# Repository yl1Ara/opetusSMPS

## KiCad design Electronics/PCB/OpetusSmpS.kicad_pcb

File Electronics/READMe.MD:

# [Interactive BOM](https://yl1ara.github.io/opetusSMPS/)

# Shopping lists and sites
components per pcb: https://www.digikey.fi/en/mylists/list/RQZPBNJORH

cables and extras: https://www.digikey.fi/en/mylists/list/IEEER25KGX

ACDC 24V 150W: https://www.mouser.fi/ProductDetail/XP-Power/AHM150PS24?qs=w%2Fv1CP2dgqrkrRjfQac7fA%3D%3D

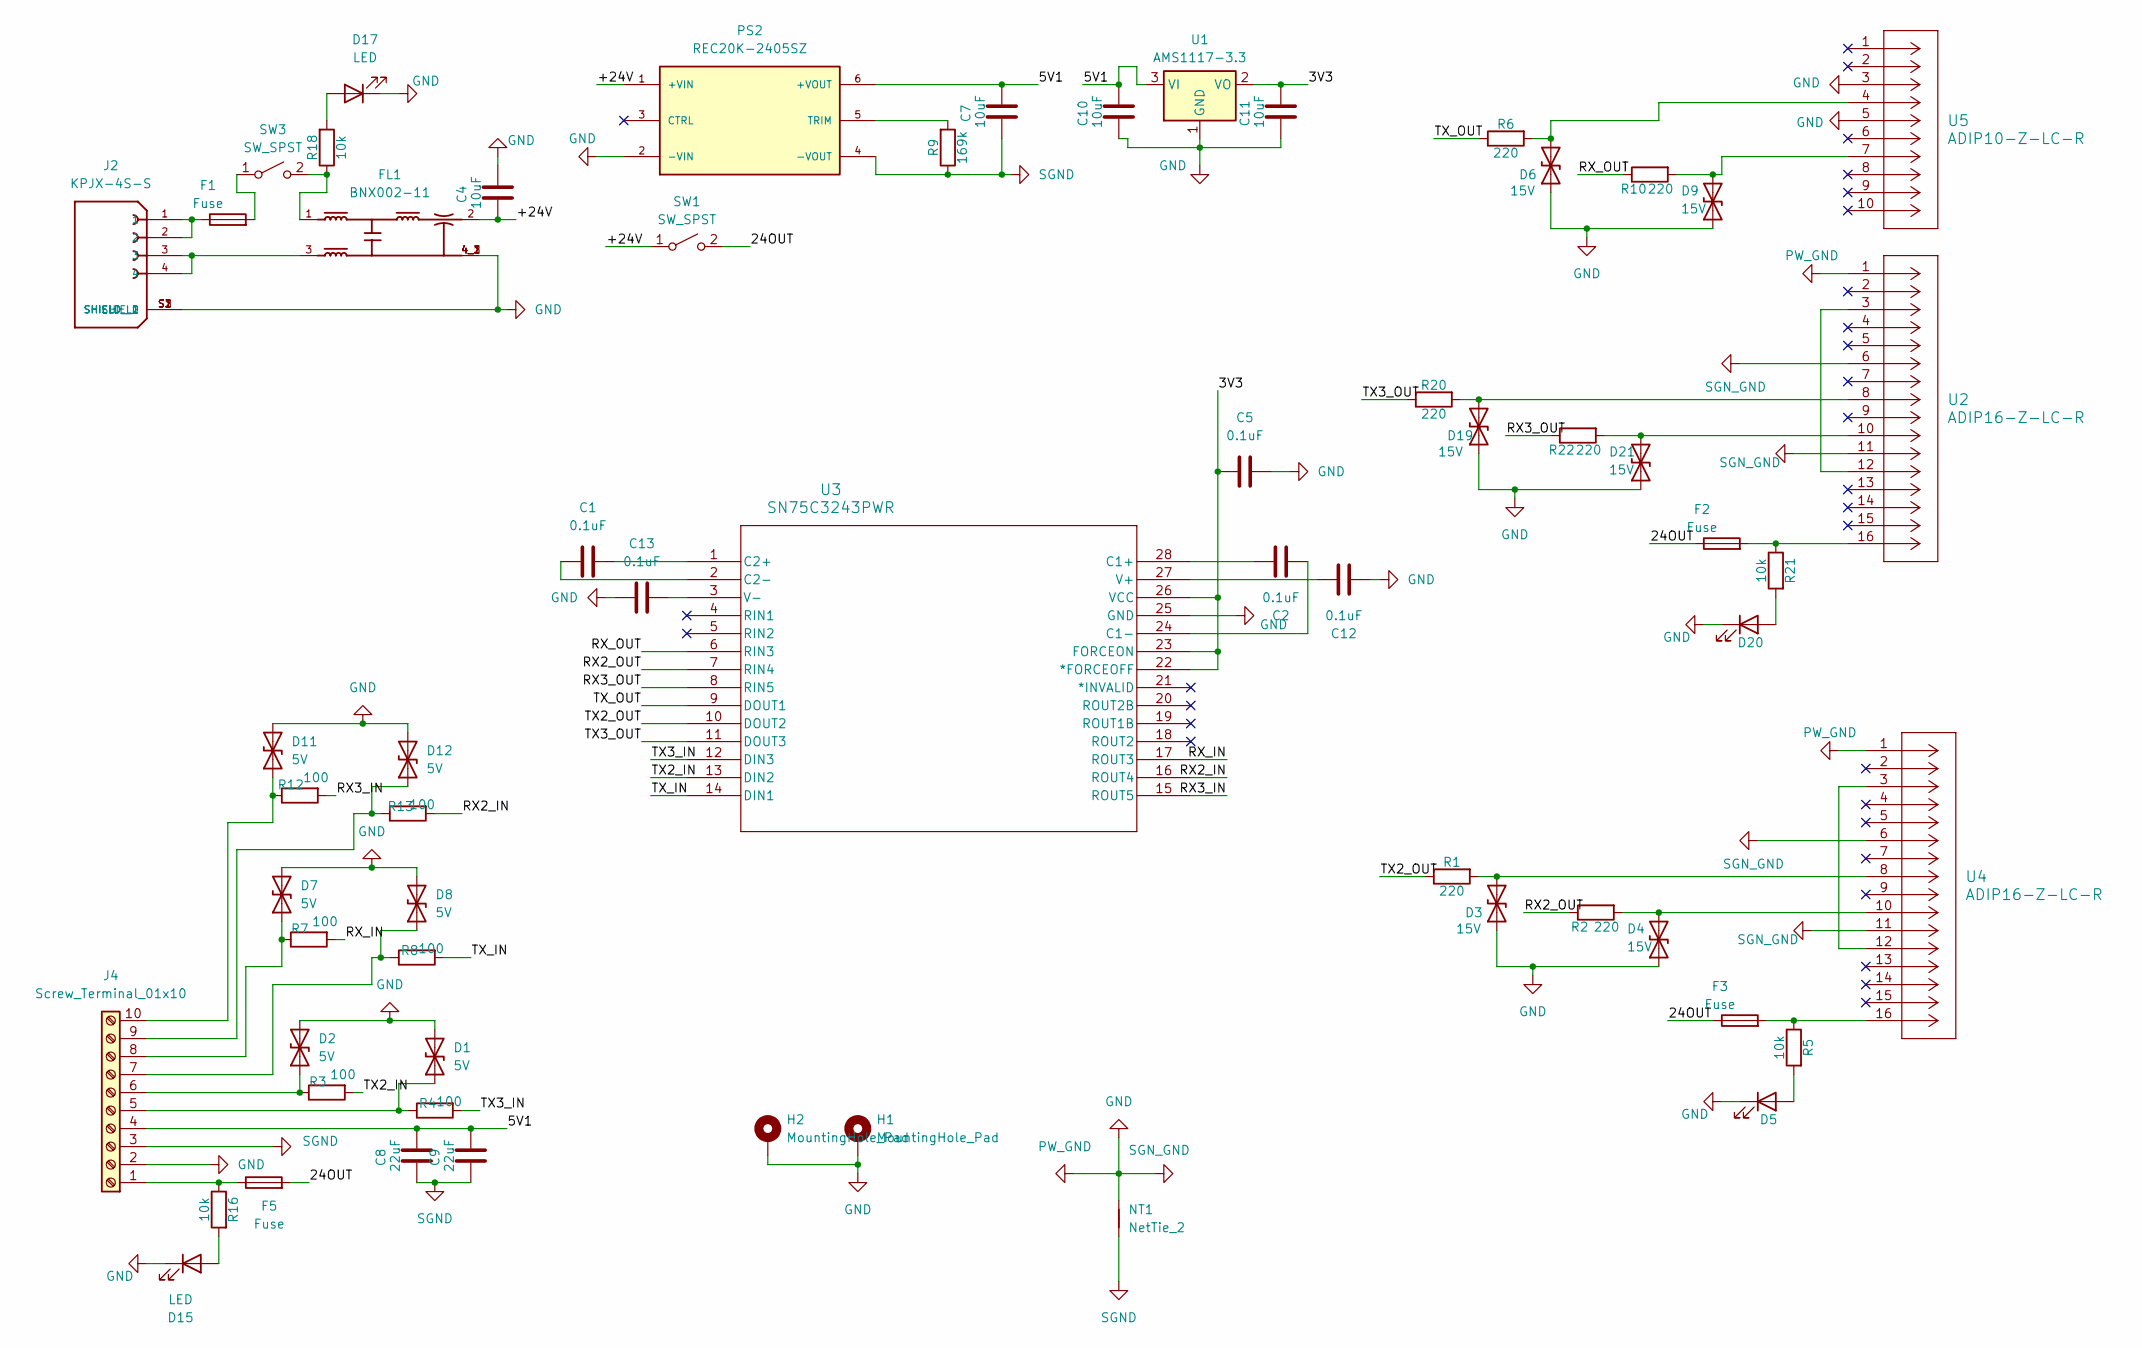
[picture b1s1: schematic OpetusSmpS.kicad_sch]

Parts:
C1, C2, C5, C12, C13: 0.1uF; C_0603_1608Metric_Pad1.08x0.95mm_HandSolder
C4, C7, C10, C11: 10uF; C_0603_1608Metric_Pad1.08x0.95mm_HandSolder
C8, C9: 22uF; C_0603_1608Metric_Pad1.08x0.95mm_HandSolder
D1, D2, D7, D8, D11, D12: 5V; D_SMA
D3, D4, D6, D9, D19, D21: 15V; D_SMB_Handsoldering
D5, D15, D17, D20: LED; PinHeader_1x02_P2.54mm_Vertical
F1: Fuse; Fuseholder_Cylinder-5x20mm_Schurter_0031_8201_Horizontal_Op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
F2, F3, F5: Fuse; FUS_RHEF100_TYCO_TYC
FL1: BNX002-11; FIL_BNX002-11; PARTREV N/A
H1, H2: MountingHole_Pad; MountingHole_4mm_Pad_Via
J2: KPJX-4S-S; KYCON_KPJX-4S-S; PARTREV A15
J4: Screw_Terminal_01x10; TerminalBlock_Phoenix_MKDS-1,5-10_1x10_P5.00mm_Horizontal
NT1: NetTie_2; NetTie-2_THT_Pad0.3mm
PS2: REC20K-2405SZ; CONV_REC20K-2405SZ; PARTREV PRELIMINARY
R1, R2, R6, R10, R20, R22: 220; R_1206_3216Metric_Pad1.30x1.75mm_HandSolder
R3, R4, R7, R8, R12, R13: 100; R_1206_3216Metric_Pad1.30x1.75mm_HandSolder
R5, R16, R18, R21: 10k; R_0805_2012Metric_Pad1.20x1.40mm_HandSolder
R9: 169k; R_0805_2012Metric_Pad1.20x1.40mm_HandSolder
SW1, SW3: SW_SPST; SolderWire-0.1sqmm_1x02_P3.6mm_D0.4mm_OD1mm
U1: AMS1117-3.3; SOT-223-3_TabPin2
U2, U4: ADIP16-Z-LC-R; CON16_300_DIP_AM_ASM
U3: SN75C3243PWR; PW28
U5: ADIP10-Z-LC-R; CON10_300_DIP_AM_ASM

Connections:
/3V3: C5.1, C11.2, U1.2 (VO), U3.22 (*FORCEOFF), U3.23 (FORCEON), U3.26 (VCC)
/5V1: C7.2, C8.2, C9.2, C10.2, J4.4, PS2.6 (+VOUT), U1.3 (VI)
/24OUT: F2.1, F3.1, F5.2, SW1.2 (B)
/+24V: C4.1, FL1.2, PS2.1 (+VIN), SW1.1 (A)
/RX2_IN: R13.2, U3.16 (ROUT4)
/RX2_OUT: R2.1, U3.7 (RIN4)
/RX3_IN: R12.2, U3.15 (ROUT5)
/RX3_OUT: R22.1, U3.8 (RIN5)
/RX_IN: R7.2, U3.17 (ROUT3)
/RX_OUT: R10.1, U3.6 (RIN3)
/TX2_IN: R3.2, U3.13 (DIN2)
/TX2_OUT: R1.1, U3.10 (DOUT2)
/TX3_IN: R4.2, U3.12 (DIN3)
/TX3_OUT: R20.1, U3.11 (DOUT3)
/TX_IN: R8.2, U3.14 (DIN1)
/TX_OUT: R6.1, U3.9 (DOUT1)
GND: C4.2, C5.2, C10.1, C11.1, C12.2, C13.2, D1.2 (A2), D2.2 (A2), D3.1 (A1), D4.1 (A1), D5.1 (K), D6.1 (A1), D7.2 (A2), D8.2 (A2), D9.1 (A1), D11.2 (A2), D12.2 (A2), D15.1 (K), D17.1 (K), D19.1 (A1), D20.1 (K), D21.1 (A1), FL1.4_1, FL1.4_2, FL1.4_3, H1.1, H2.1, J2.S1 (SHIELD), J2.S2 (SHIELD__1), J2.S3 (SHIELD__2), J4.2, NT1.2, PS2.2 (-VIN), U1.1 (GND), U2.1, U2.6, U2.11, U3.25 (GND), U4.1, U4.6, U4.11, U5.3, U5.5
unnamed: D1.1 (A1), J4.5, R4.1
unnamed: D2.1 (A1), J4.6, R3.1
unnamed: D3.2 (A2), R1.2, U4.8
unnamed: D4.2 (A2), R2.2, U4.10
unnamed: D5.2 (A), R5.2
unnamed: D6.2 (A2), R6.2, U5.4
unnamed: D7.1 (A1), J4.8, R7.1
unnamed: D8.1 (A1), J4.7, R8.1
unnamed: D9.2 (A2), R10.2, U5.7
unnamed: D11.1 (A1), J4.10, R12.1
unnamed: D12.1 (A1), J4.9, R13.1
unnamed: D15.2 (A), R16.2
unnamed: D17.2 (A), R18.2
unnamed: D19.2 (A2), R20.2, U2.8
unnamed: D20.2 (A), R21.2
unnamed: D21.2 (A2), R22.2, U2.10
unnamed: F1.1, J2.1, J2.2
unnamed: F2.2, R21.1, U2.16
unnamed: F3.2, R5.1, U4.16
unnamed: FL1.3, J2.3, J2.4
unnamed: F5.1, J4.1, R16.1
unnamed: PS2.5 (TRIM), R9.2
unnamed: F1.2, SW3.1 (A)
unnamed: FL1.1, R18.1, SW3.2 (B)
unnamed: U2.3, U2.12
unnamed: C2.1, U3.28 (C1+)
unnamed: C2.2, U3.24 (C1-)
unnamed: C1.2, U3.1 (C2+)
unnamed: C1.1, U3.2 (C2-)
unnamed: C12.1, U3.27 (V+)
unnamed: C13.1, U3.3 (V-)
unnamed: U4.3, U4.12
SGND: C7.1, C8.1, C9.1, J4.3, NT1.1, PS2.4 (-VOUT), R9.1

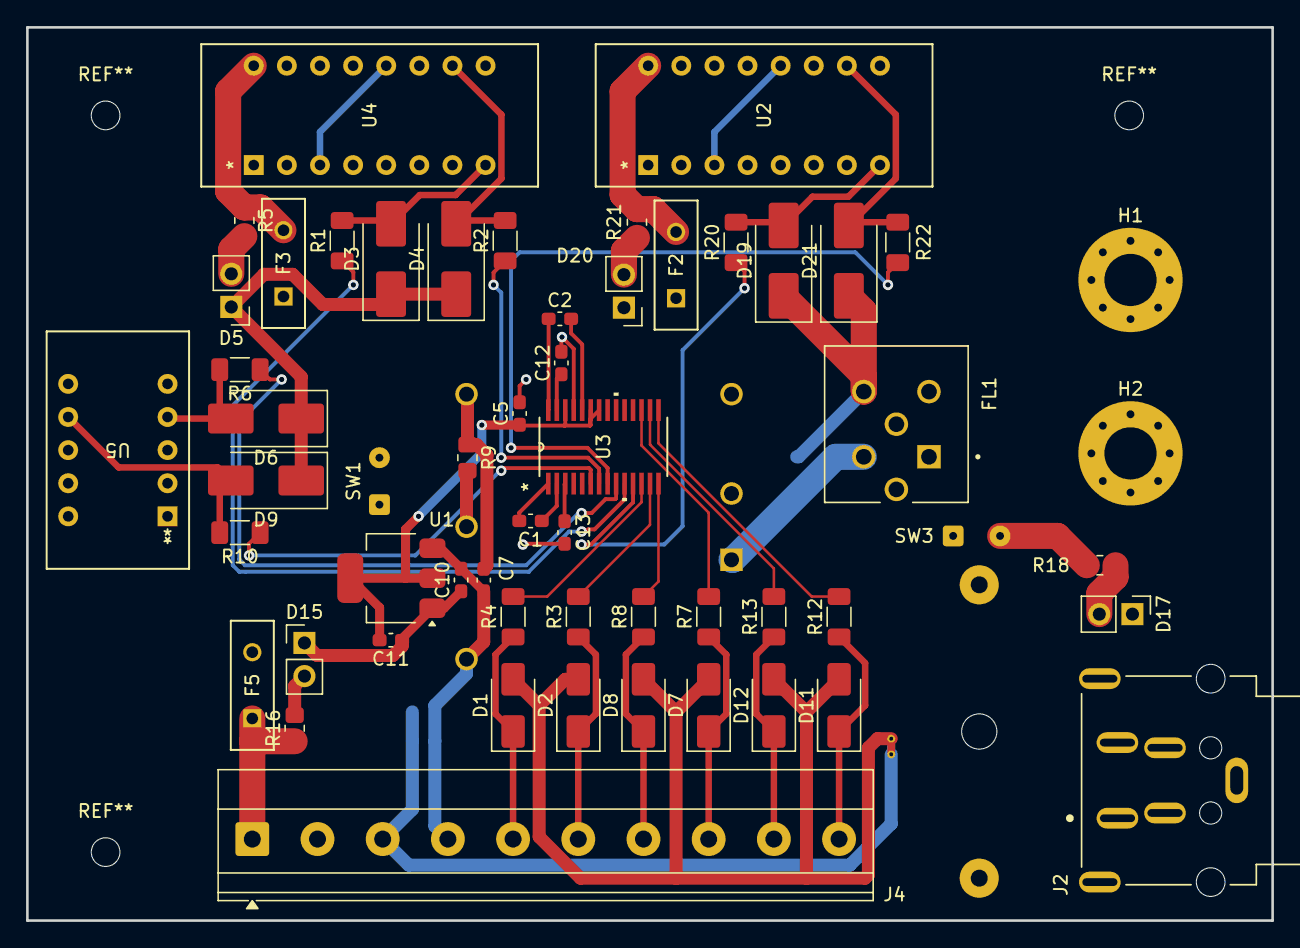
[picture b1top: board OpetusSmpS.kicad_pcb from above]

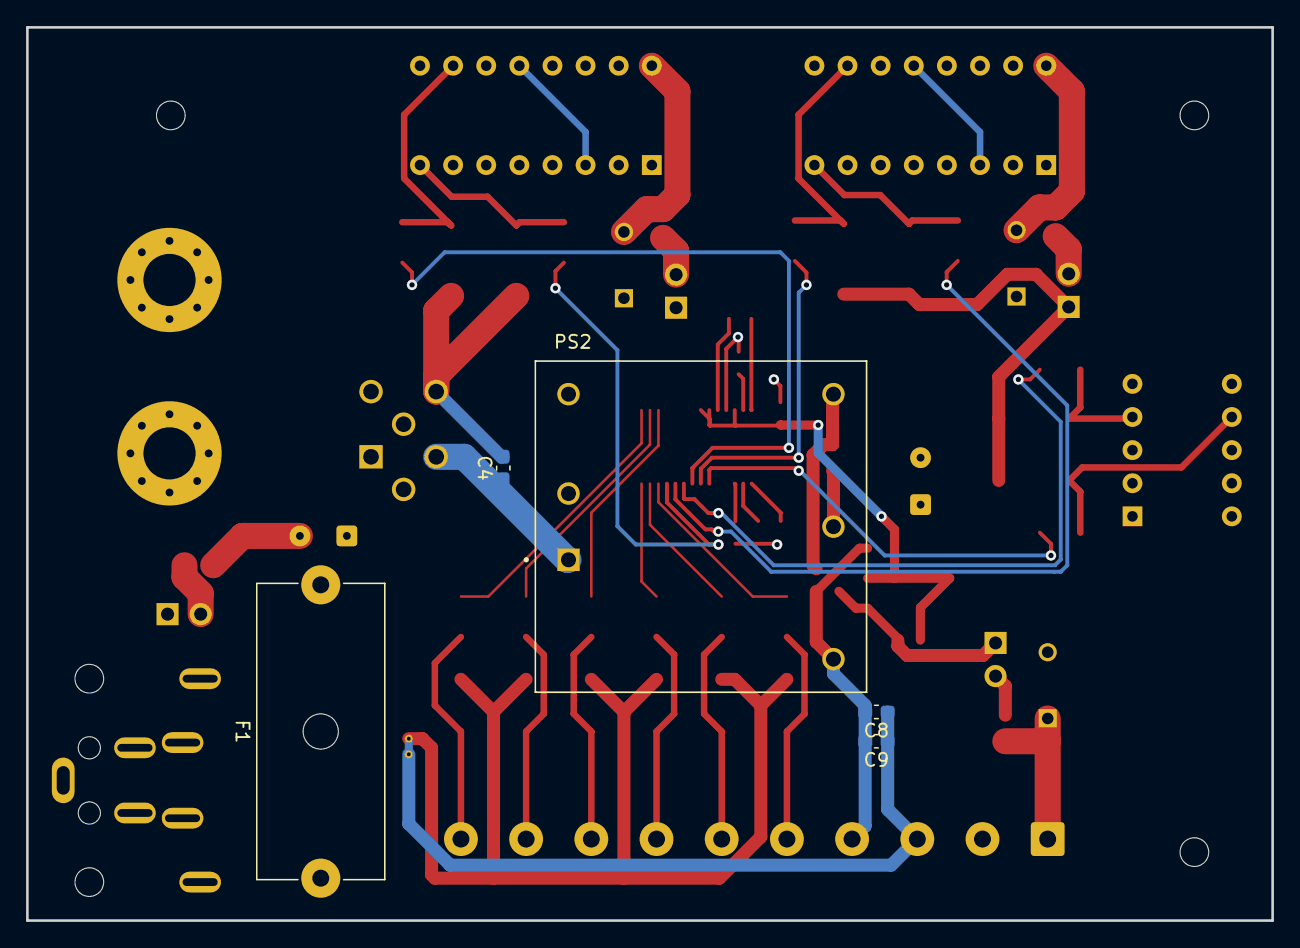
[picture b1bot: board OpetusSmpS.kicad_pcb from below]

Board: 4 copper layers, 95.5 x 68.5 mm, 62 parts (5 on the bottom side), 50 nets.

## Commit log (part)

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2026-01-16 Initial
2026-01-16 Add README file with project title
2026-01-16 Add README file with lists and relevant links
2026-01-16 Add new lines for better readability in README
2026-01-16 Update terminology in README for clarity
2026-01-16 Revise README structure to include Interactive BOM section and improve organization
2026-01-16 Refactor Interactive BOM section header and link for consistency
2026-01-16 Fix link in Interactive BOM section to include raw parameter for proper rendering
2026-01-16 Refactor code structure for improved readability and maintainability
2026-01-16 Implement feature X to enhance user experience and fix bug Y in module Z
2026-01-16 Update Interactive BOM link to point to the correct URL for proper access
2026-01-16 Remove outdated links from README
2026-03-08 Fix typo in components per pcb link in README
